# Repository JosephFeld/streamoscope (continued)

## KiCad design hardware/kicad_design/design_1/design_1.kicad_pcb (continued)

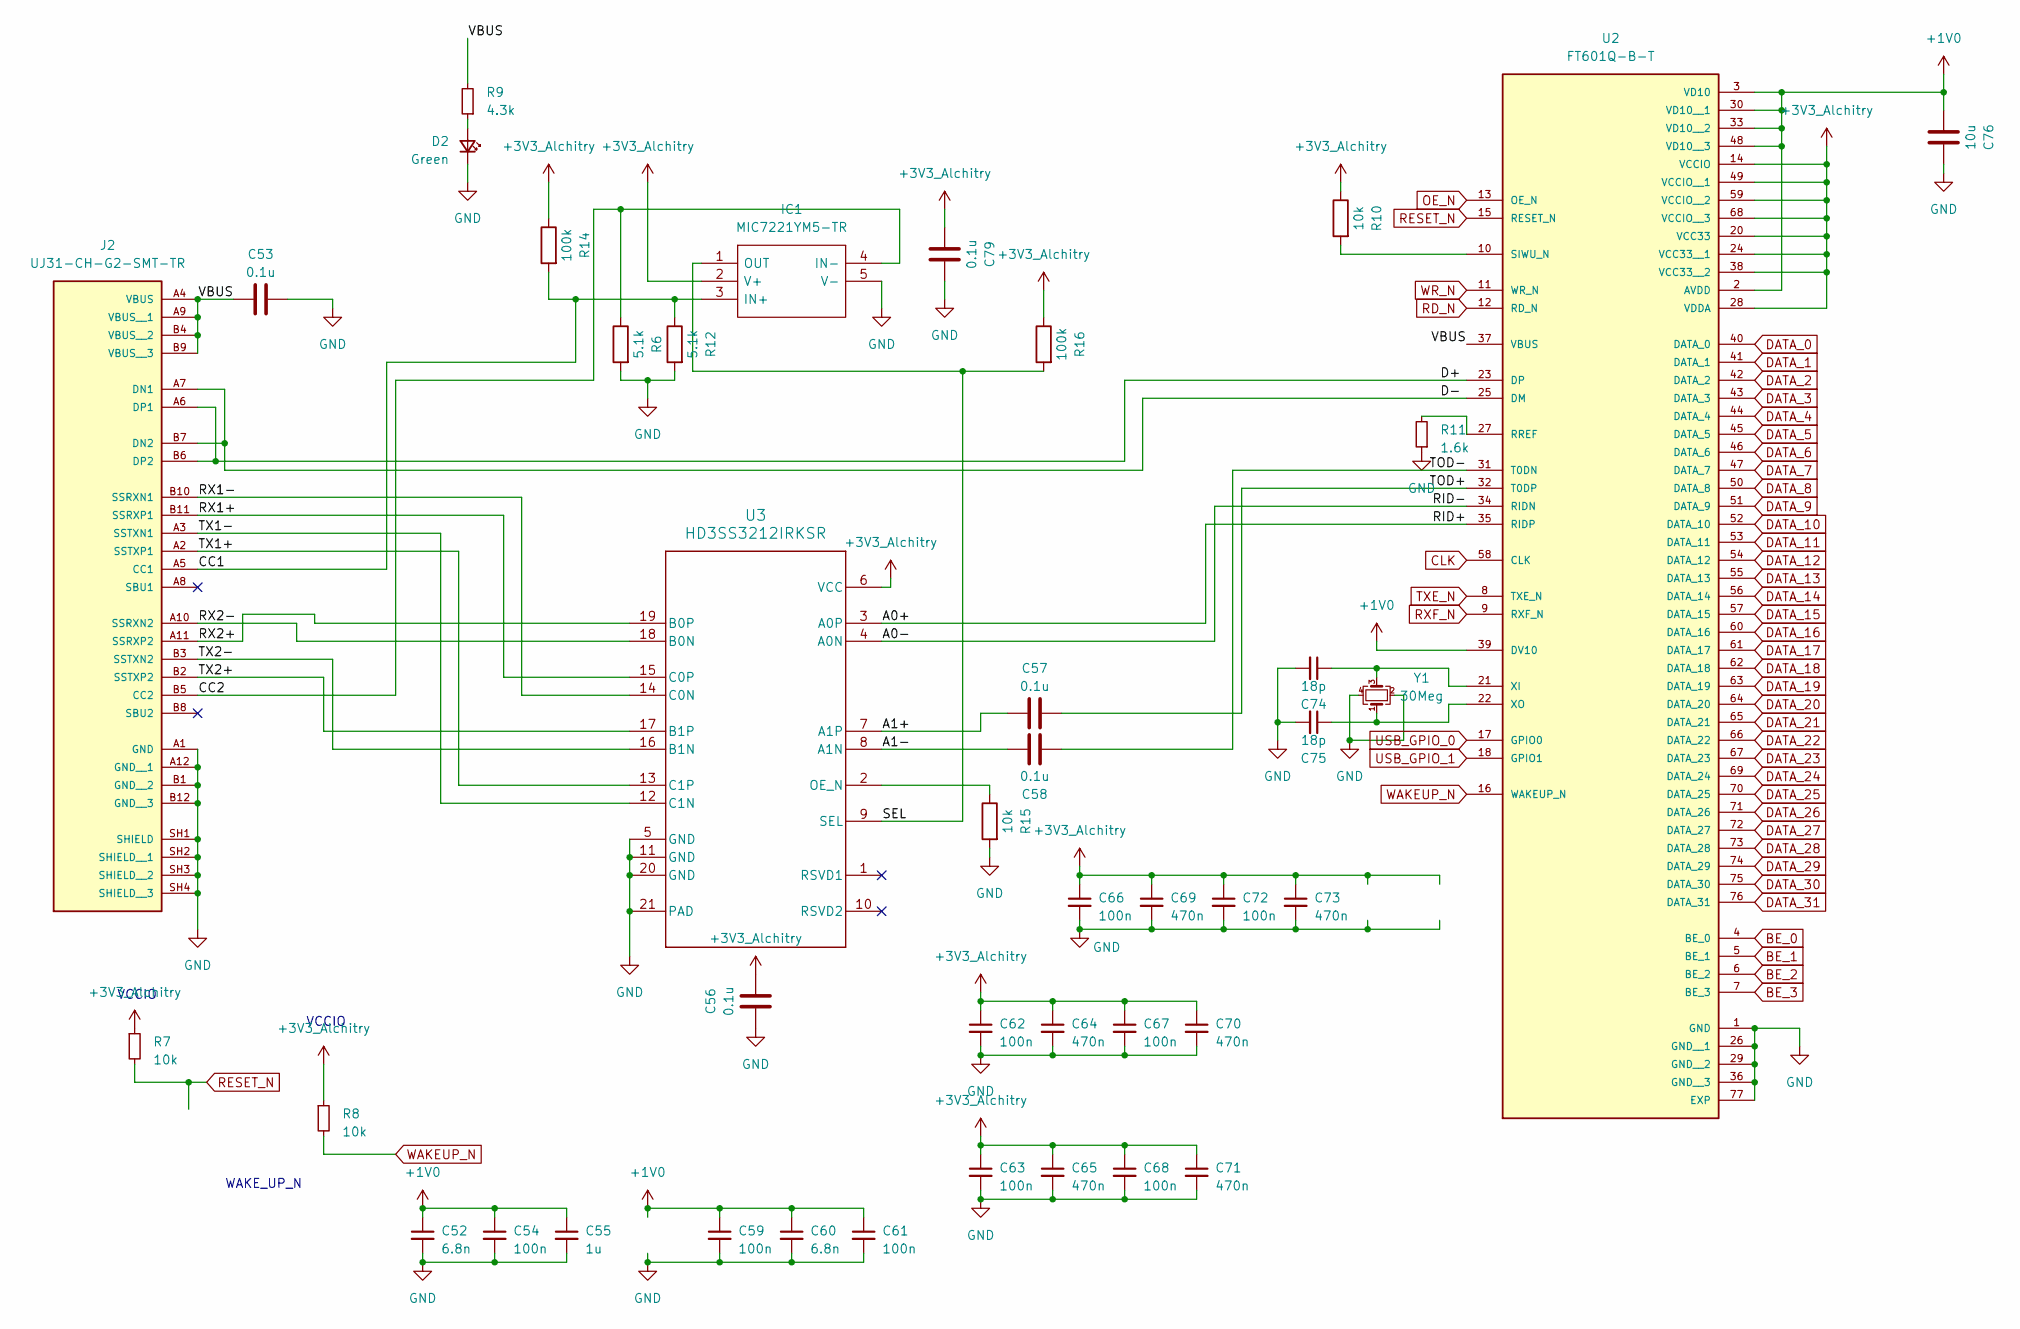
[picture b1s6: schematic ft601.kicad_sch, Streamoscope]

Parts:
C52, C60: 6.8n; C_0402_1005Metric_Pad0.74x0.62mm_HandSolder
C53, C56, C57, C58, C79: 0.1u; C_0402_1005Metric_Pad0.74x0.62mm_HandSolder
C54, C59, C61, C62, C63, C66, C67, C68, C72: 100n; C_0402_1005Metric_Pad0.74x0.62mm_HandSolder
C55: 1u; C_0402_1005Metric_Pad0.74x0.62mm_HandSolder
C64, C65, C69, C70, C71, C73: 470n; C_0402_1005Metric_Pad0.74x0.62mm_HandSolder
C74, C75: 18p; C_0402_1005Metric_Pad0.74x0.62mm_HandSolder
C76: 10u; C_0402_1005Metric_Pad0.74x0.62mm_HandSolder
D2: Green; LED_0603_1608Metric
IC1: MIC7221YM5-TR; SOT95P280X130-5N; Mouser Part Number 998-MIC7221YM5TR
J2: UJ31-CH-G2-SMT-TR; CUI_UJ31-CH-G2-SMT-TR; PART_REV 1.01
R6, R12: 5.1k; R_0402_1005Metric_Pad0.72x0.64mm_HandSolder
R7, R8, R10, R15: 10k; R_0402_1005Metric_Pad0.72x0.64mm_HandSolder
R9: 4.3k; R_0402_1005Metric_Pad0.72x0.64mm_HandSolder
R11: 1.6k; R_0402_1005Metric_Pad0.72x0.64mm_HandSolder
R14, R16: 100k; R_0402_1005Metric_Pad0.72x0.64mm_HandSolder
U2: FT601Q-B-T; QFN40P900X900X100-77N; PARTREV 1.05
U3: HD3SS3212IRKSR; SN74HCS541RKSR
Y1: 30Meg; Crystal_SMD_3225-4Pin_3.2x2.5mm; MPN 830059646

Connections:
+1V0: C52.1, C54.1, C55.1, C59.1, C60.1, C61.1, C76.1, U2.2 (AVDD), U2.3 (VD10), U2.30 (VD10__1), U2.33 (VD10__2), U2.39 (DV10), U2.48 (VD10__3)
+3V3_Alchitry: C56.2, C62.1, C63.1, C64.1, C65.1, C66.1, C67.1, C68.1, C69.1, C70.1, C71.1, C72.1, C73.1, C79.1, IC1.2 (V+), R7.1, R8.1, R10.1, R14.1, R16.1, U2.14 (VCCIO), U2.20 (VCC33), U2.24 (VCC33__1), U2.28 (VDDA), U2.38 (VCC33__2), U2.49 (VCCIO__1), U2.59 (VCCIO__2), U2.68 (VCCIO__3), U3.6 (VCC); also elsewhere on the board
/ft601/A0+: U2.35 (RIDP), U3.3 (A0P)
/ft601/A0-: U2.34 (RIDN), U3.4 (A0N)
/ft601/A1+: C57.1, U3.7 (A1P)
/ft601/A1-: C58.1, U3.8 (A1N)
/ft601/CC1: IC1.3 (IN+), J2.A5 (CC1), R12.1, R14.2
/ft601/CC2: IC1.4 (IN-), J2.B5 (CC2), R6.1
/ft601/D+: J2.A6 (DP1), J2.B6 (DP2), U2.23 (DP)
/ft601/D-: J2.A7 (DN1), J2.B7 (DN2), U2.25 (DM)
/ft601/RX1+: J2.B11 (SSRXP1), U3.15 (C0P)
/ft601/RX1-: J2.B10 (SSRXN1), U3.14 (C0N)
/ft601/RX2+: J2.A11 (SSRXP2), U3.19 (B0P)
/ft601/RX2-: J2.A10 (SSRXN2), U3.18 (B0N)
/ft601/SEL: IC1.1 (OUT), R16.2, U3.9 (SEL)
/ft601/TOD+: C57.2, U2.32 (T0DP)
/ft601/TOD-: C58.2, U2.31 (T0DN)
/ft601/TX1+: J2.A2 (SSTXP1), U3.13 (C1P)
/ft601/TX1-: J2.A3 (SSTXN1), U3.12 (C1N)
/ft601/TX2+: J2.B2 (SSTXP2), U3.17 (B1P)
/ft601/TX2-: J2.B3 (SSTXN2), U3.16 (B1N)
/ft601/VBUS: C53.1, J2.A4 (VBUS), J2.A9 (VBUS__1), J2.B4 (VBUS__2), J2.B9 (VBUS__3), R9.2, U2.37 (VBUS)
BE_0: U2.4 (BE_0); also elsewhere on the board
BE_1: U2.5 (BE_1); also elsewhere on the board
BE_2: U2.6 (BE_2); also elsewhere on the board
BE_3: U2.7 (BE_3); also elsewhere on the board
CLK: U2.58 (CLK); also elsewhere on the board
DATA_0: U2.40 (DATA_0); also elsewhere on the board
DATA_1: U2.41 (DATA_1); also elsewhere on the board
DATA_2: U2.42 (DATA_2); also elsewhere on the board
DATA_3: U2.43 (DATA_3); also elsewhere on the board
DATA_4: U2.44 (DATA_4); also elsewhere on the board
DATA_5: U2.45 (DATA_5); also elsewhere on the board
DATA_6: U2.46 (DATA_6); also elsewhere on the board
DATA_7: U2.47 (DATA_7); also elsewhere on the board
DATA_8: U2.50 (DATA_8); also elsewhere on the board
DATA_9: U2.51 (DATA_9); also elsewhere on the board
DATA_10: U2.52 (DATA_10); also elsewhere on the board
DATA_11: U2.53 (DATA_11); also elsewhere on the board
DATA_12: U2.54 (DATA_12); also elsewhere on the board
DATA_13: U2.55 (DATA_13); also elsewhere on the board
DATA_14: U2.56 (DATA_14); also elsewhere on the board
DATA_15: U2.57 (DATA_15); also elsewhere on the board
DATA_16: U2.60 (DATA_16); also elsewhere on the board
DATA_17: U2.61 (DATA_17); also elsewhere on the board
DATA_18: U2.62 (DATA_18); also elsewhere on the board
DATA_19: U2.63 (DATA_19); also elsewhere on the board
DATA_20: U2.64 (DATA_20); also elsewhere on the board
DATA_21: U2.65 (DATA_21); also elsewhere on the board
DATA_22: U2.66 (DATA_22); also elsewhere on the board
DATA_23: U2.67 (DATA_23); also elsewhere on the board
DATA_24: U2.69 (DATA_24); also elsewhere on the board
DATA_25: U2.70 (DATA_25); also elsewhere on the board
DATA_26: U2.71 (DATA_26); also elsewhere on the board
DATA_27: U2.72 (DATA_27); also elsewhere on the board
DATA_28: U2.73 (DATA_28); also elsewhere on the board
DATA_29: U2.74 (DATA_29); also elsewhere on the board
DATA_30: U2.75 (DATA_30); also elsewhere on the board
DATA_31: U2.76 (DATA_31); also elsewhere on the board
GND: C52.2, C53.2, C54.2, C55.2, C56.1, C59.2, C60.2, C61.2, C62.2, C63.2, C64.2, C65.2, C66.2, C67.2, C68.2, C69.2, C70.2, C71.2, C72.2, C73.2, C74.2, C75.2, C76.2, C79.2, D2.1 (K), IC1.5 (V-), J2.A1 (GND), J2.A12 (GND__1), J2.B1 (GND__2), J2.B12 (GND__3), J2.SH1 (SHIELD), J2.SH2 (SHIELD__1), J2.SH3 (SHIELD__2), J2.SH4 (SHIELD__3), R6.2, R11.1, R12.2, R15.2, U2.1 (GND), U2.26 (GND__1), U2.29 (GND__2), U2.36 (GND__3), U2.77 (EXP), U3.5 (GND), U3.11 (GND), U3.20 (GND), U3.21 (PAD), Y1.2, Y1.4; also elsewhere on the board
unnamed: D2.2 (A), R9.1
unnamed: R11.2, U2.27 (RREF)
unnamed: R10.2, U2.10 (SIWU_N)
unnamed: C74.1, U2.21 (XI), Y1.3
unnamed: C75.1, U2.22 (XO), Y1.1
unnamed: R15.1, U3.2 (OE_N)
OE_N: U2.13 (OE_N); also elsewhere on the board
RD_N: U2.12 (RD_N); also elsewhere on the board
RESET_N: R7.2, U2.15 (RESET_N); also elsewhere on the board
RXF_N: U2.9 (RXF_N); also elsewhere on the board
TXE_N: U2.8 (TXE_N); also elsewhere on the board
USB_GPIO_0: U2.17 (GPIO0); also elsewhere on the board
USB_GPIO_1: U2.18 (GPIO1); also elsewhere on the board
WAKEUP_N: R8.2, U2.16 (WAKEUP_N); also elsewhere on the board
WR_N: U2.11 (WR_N); also elsewhere on the board

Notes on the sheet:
VCCIO
WAKE_UP_N

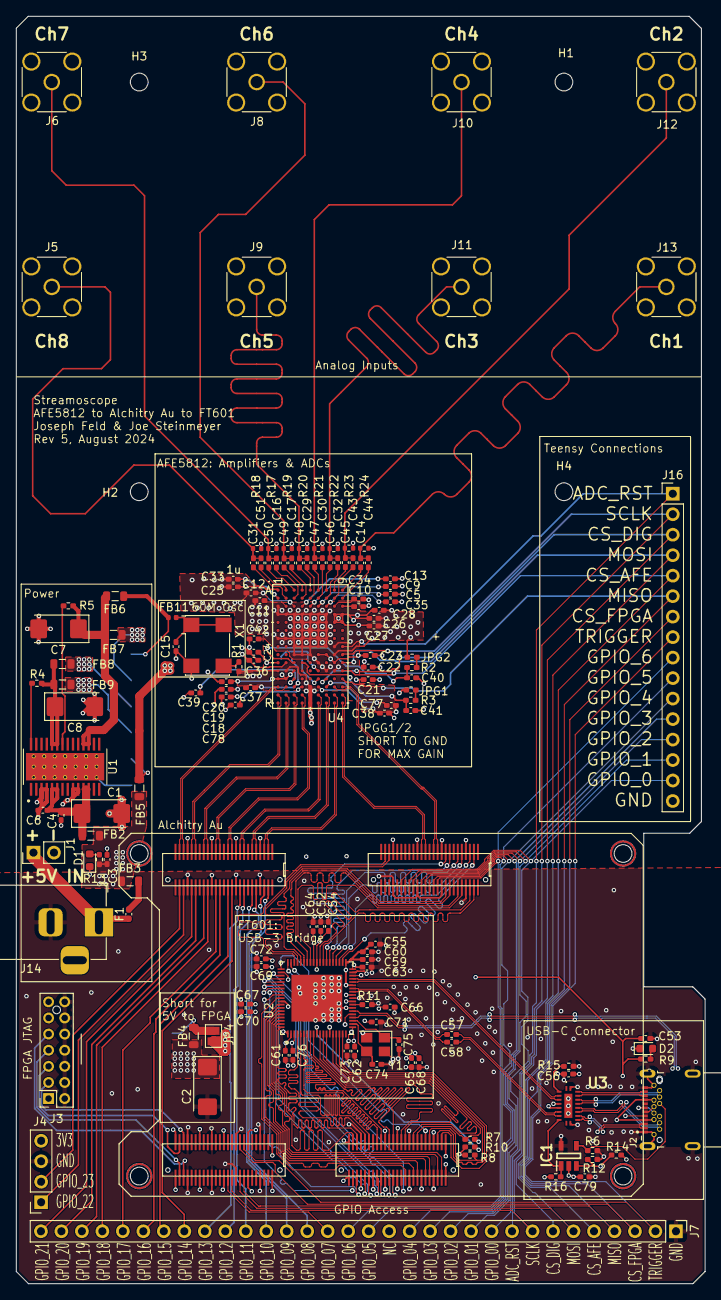
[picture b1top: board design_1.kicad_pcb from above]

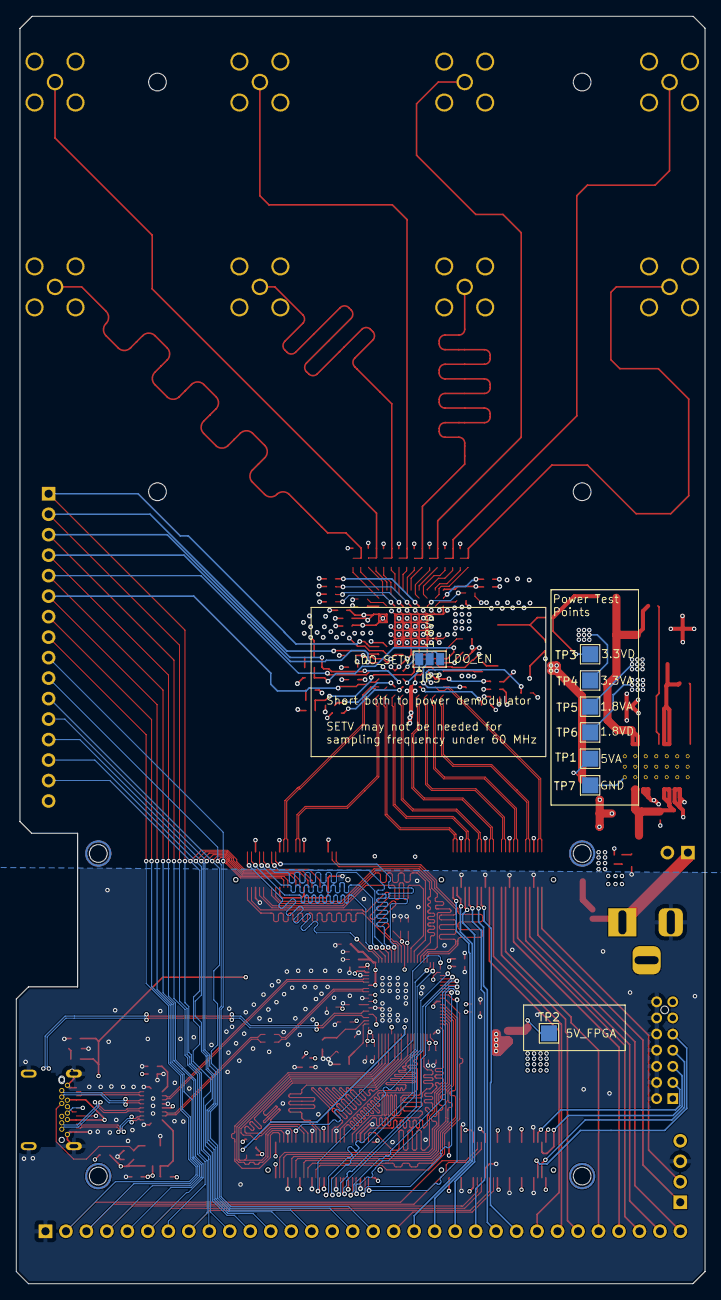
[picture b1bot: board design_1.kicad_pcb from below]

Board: 4 copper layers, 85.4 x 157.2 mm, 153 parts (9 on the bottom side), 193 nets.

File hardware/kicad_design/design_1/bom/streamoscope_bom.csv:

Id,Designator,Footprint,Quantity,Designation,Supplier and ref,supplemental parts,
1,J7,PinHeader_1x32_P2.54mm_Vertical,1,Conn_01x32_Pin,https://www.mouser.com/ProductDetail/TE-Connectivity/3-82693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,,
2,F1,Fuse_0402_1005Metric_Pad0.77x0.64mm_HandSolder,1,Fuse,https://www.mouser.com/ProductDetail/Littelfuse/043502.5KRHF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,,
3,J16,PinHeader_1x16_P2.54mm_Vertical,1,Conn_01x16_Pin,https://www.mouser.com/ProductDetail/Amphenol-FCI/68024-116H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,https://www.mouser.com/ProductDetail/Samtec/IDSS-16-D-20.00?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,
4,J15,AMPHENOL_12401899E412A,1,USB_C_Receptacle,https://www.mouser.com/ProductDetail/Amphenol-Commercial-Pro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,,
5,"C33,C31,C17,C16,C42,C29,C30,C44,C32,C55,C43",C_0402_1005Metric_Pad0.74x0.62mm_HandSolder,11,1u,https://www.mouser.com/ProductDetail/KYOCERA-AVX/KGM05AR51A1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,,
6,"R7,R8,R10,R15",R_0402_1005Metric_Pad0.72x0.64mm_HandSolder,4,10k,https://www.mouser.com/ProductDetail/TE-Connectivity-Holswor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,,
7,"C9,C35,C10,C11,C34,C12,C5,C13",C_0402_1005Metric_Pad0.74x0.62mm_HandSolder,8,15n,https://www.mouser.com/ProductDetail/KEMET/C0402C153K3RACTU?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,,
8,"C38,C15,C47,C53,C20,C23,C78,C3,C40,C50,C58,C19,C41,C26,C45,C51,C79,C46,C27,C14,C39,C36,C77,C28,C24,C25,C57,C22,C4,C48,C21,C49,C18,C37,C56",C_0402_1005Metric_Pad0.74x0.62mm_HandSolder,35,0.1u,https://www.mouser.com/ProductDetail/KYOCERA-AVX/0402X7R104K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,,
9,J1,PinHeader_1x02_P2.54mm_Vertical,1,Conn_01x02_Pin,,,
10,"C7,C2,C8,C1",CP_EIA-6032-20_AVX-F,4,22u,https://www.mouser.com/ProductDetail/KYOCERA-AVX/TPSC226K016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,,
11,"FB3,FB7,FB5,FB9,FB8,FB6,FB2,FB4",L_0805_2012Metric,8,FerriteBead,https://www.mouser.com/ProductDetail/Laird-Performance-Mater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,,
12,"J11,J8,J13,J6,J10,J9,J5,J12",SMA_Amphenol_132134_Vertical,8,Conn_Coaxial,https://www.mouser.com/ProductDetail/LPRS/SMA-CONNECTOR?qs=j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,,
13,FB11,L_0402_1005Metric,1,FerriteBead,https://www.mouser.com/ProductDetail/Murata-Electronics/BLM1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,,
14,"C59,C61,C72,C54,C62,C63,C68,C66,C67",C_0402_1005Metric_Pad0.74x0.62mm_HandSolder,9,100n,https://www.mouser.com/ProductDetail/KYOCERA-AVX/0402X7R104K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,,
15,"JPG1,JPG2",R_0402_1005Metric_Pad0.72x0.64mm_HandSolder,2,0,https://www.mouser.com/ProductDetail/Vishay-Dale/CRCW0402000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,,
16,"C73,C70,C71,C69,C65,C64",C_0402_1005Metric_Pad0.74x0.62mm_HandSolder,6,470n,https://www.mouser.com/ProductDetail/KYOCERA-AVX/0402ZC474KA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,,
17,R1,R_0402_1005Metric_Pad0.72x0.64mm_HandSolder,1,49.9,https://www.mouser.com/ProductDetail/Panasonic/ERA-2AED49R9X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,,
18,"D2,D1",LED_0603_1608Metric,2,Green,https://www.mouser.com/ProductDetail/ROHM-Semiconductor/SMLD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,,
19,"R3,R2",R_0402_1005Metric_Pad0.72x0.64mm_HandSolder,2,200,https://www.mouser.com/ProductDetail/Vishay-Dale/CRCW0402200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,,
20,X1,Oscillator_SMD_Abracon_ASV-4Pin_7.0x5.1mm,1,XO32,https://www.mouser.com/ProductDetail/ABRACON/ASV-60.000MHZ-E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,,
21,U1,IC_TPS61196PWPRQ1,1,TPS767D318PWPR,https://www.mouser.com/ProductDetail/Texas-Instruments/TPS76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,,
22,J14,BarrelJack_Horizontal,1,Barrel_Jack,https://www.mouser.com/ProductDetail/Wurth-Elektronik/694106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,alt:,https://www.digikey.com/en/products/detail/cui-devices/PJ-00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
23,IC1,SOT95P280X130-5N,1,MIC7221YM5-TR,https://www.mouser.com/ProductDetail/Microchip-Technology/MI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,,
24,"C52,C60",C_0402_1005Metric_Pad0.74x0.62mm_HandSolder,2,6.8n,https://www.mouser.com/ProductDetail/KYOCERA-AVX/04025C682K4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,,
25,U2,QFN40P900X900X100-77N,1,FT601Q-B-T,https://www.mouser.com/ProductDetail/FTDI/FT601Q-B-T?qs=p9T7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,,
26,U4,ZCF135_TEX_NO_PASTE,1,AFE5812ZCF,https://www.mouser.com/ProductDetail/Texas-Instruments/AFE58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,,
27,"R4,R5",R_0402_1005Metric_Pad0.72x0.64mm_HandSolder,2,250K,https://www.mouser.com/ProductDetail/Panasonic/ERJ-PA2D2493X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,,
28,"R12,R6",R_0402_1005Metric_Pad0.72x0.64mm_HandSolder,2,5.1k,https://www.mouser.com/ProductDetail/Vishay-Dale/CRCW04025K1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,,
29,J3,PinSocket_2x07_P2.00mm_Vertical,1,Conn_02x07_Odd_Even,https://www.mouser.com/ProductDetail/Molex/87831-1435?qs=kNS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,,
30,"R16,R14",R_0402_1005Metric_Pad0.72x0.64mm_HandSolder,2,100k,https://www.mouser.com/ProductDetail/Panasonic/ERJ-H2RD1003X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,,
31,U3,SN74HCS541RKSR,1,HD3SS3212IRKSR,https://www.mouser.com/ProductDetail/Texas-Instruments/HD3SS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,,
32,"C75,C74",C_0402_1005Metric_Pad0.74x0.62mm_HandSolder,2,18p,https://www.mouser.com/ProductDetail/KYOCERA-AVX/04025A180GA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,,
33,C6,C_0402_1005Metric_Pad0.74x0.62mm_HandSolder,1,0.1u ,https://www.mouser.com/ProductDetail/KYOCERA-AVX/0402X7R104K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,,
34,C76,C_0402_1005Metric_Pad0.74x0.62mm_HandSolder,1,10u,https://www.mouser.com/ProductDetail/KYOCERA-AVX/04024D106MA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,,
35,"R9,R13",R_0402_1005Metric_Pad0.72x0.64mm_HandSolder,2,4.3k,https://www.mouser.com/ProductDetail/Vishay-Dale/CRCW04024K3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,,
36,R11,R_0402_1005Metric_Pad0.72x0.64mm_HandSolder,1,1.6k,https://www.mouser.com/ProductDetail/Vishay-Dale/CRCW04021K6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,,
37,Y1,Crystal_SMD_3225-4Pin_3.2x2.5mm,1,30Meg,https://www.mouser.com/ProductDetail/Wurth-Elektronik/830059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,,
38,J4,PinSocket_1x04_P2.54mm_Vertical,1,Conn_01x04_Pin,https://www.mouser.com/ProductDetail/Amphenol-FCI/68000-204H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,,
39,B1,Element_no_top,1,Alchitry_Element_AU,https://www.mouser.com/ProductDetail/SparkFun/DEV-16527?qs=W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,,
40,TP3,TestPoint_Pad_2.0x2.0mm,1,3.3VA,,,
41,TP6,TestPoint_Pad_2.0x2.0mm,1,1.8VD,,,
42,TP7,TestPoint_Pad_2.0x2.0mm,1,GND,,,
43,TP4,TestPoint_Pad_2.0x2.0mm,1,3.3VD,,,
44,TP5,TestPoint_Pad_2.0x2.0mm,1,1.8VA,,,
45,TP1,TestPoint_Pad_2.0x2.0mm,1,5VA,,,
46,TP2,TestPoint_Pad_2.0x2.0mm,1,5V,,,

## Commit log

2024-08-23 vivado streamoscope tcl file
2024-08-23 adc lvds modified IP
2024-08-23 fixed file paths
2024-08-23 fixed file paths again
2024-08-23 lets go third times the charm on these file paths
2024-08-23 file paths are fixed for real (i think)
2024-08-23 maybe file paths are right now...
2024-08-23 updated README with instructions for vivado setup
2024-08-23 minor readme update
2024-08-23 minor readme update better english
2024-08-23 more readme context
2024-08-23 python streamoscope reading example
2024-08-23 rename ipynb
2024-08-23 python instructions
2024-08-23 added zadig image and teensy code
2024-08-23 added FPGA configurations
2024-08-23 teensy section of readme
2024-08-23 board files
2024-08-23 gerbers
2024-08-23 lots more readme updates
2024-08-23 readme figures from thesis
2024-08-23 more enthusiastic intro. could be more enthusiastic though
2024-08-28 new build script
2024-08-28 Update README.md
    new hopefully working thing readme for hopefully working tcl script!
2024-08-28 log files I dont want
2024-08-28 change to int value
2024-08-28 xci with integer instead of bitstring
2024-08-30 fine ps mode on feedback clock
2024-08-30 xdc for rev 4 board
2024-08-30 rev4 verilog
2024-08-30 8 channel ila more probes
2024-08-30 new afe thing
2024-09-05 rev 5 board with termination resistors, through hole usb c, and minor fixes
2024-09-05 cleaned up teensy
2024-09-05 rev 5 gerbers
2024-09-05 rev 4/5 board bitstreams
2024-09-05 default using trigger directly in sv
2024-09-05 updated through hole usb c bom
